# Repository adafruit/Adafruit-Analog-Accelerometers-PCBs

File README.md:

# PCBs for the Adafruit Analog Accelerometers - ADXL335, ADXL377 and ADXL326

<a href="http://www.adafruit.com/products/163"><br/>Click here to purchase one from the Adafruit shop</a>

* [ADXL335 - 5V ready triple-axis accelerometer (+-3g analog out)](https://www.adafruit.com/products/163)
* [ADXL326 - 5V ready triple-axis accelerometer (+-16g analog out)](https://www.adafruit.com/product/1018)
* [ADXL377 - High-G Triple-Axis Accelerometer (+-200g Analog Out)](https://www.adafruit.com/product/1413)

We've updated our favorite triple-axis accelerometer to now have an on-board 3.3V regulator - making it a perfect choice for interfacing with a 5V microcontroller such as the Arduino. This breakout comes with 3 analog outputs for X, Y and Z axis measurements on a 0.75"x0.75" breakout board. The ADXL335 is the latest and greatest from Analog Devices, known for their exceptional quality MEMS devices. The VCC takes up to 5V in and regulates it to 3.3V with an output pin. The analog outputs are ratiometric: that means that 0g measurement output is always at half of the 3.3V output (1.65V), -3g is at 0v and 3g is at 3.3V with full scaling in between.

Fully assembled and tested. Comes with 8 pin 0.1" standard header in case you want to use it with a breadboard or perfboard. Two 2mm (0.08") mounting holes for easy attachment.

The XYZ filter capacitors are 0.1uF for a 50 Hz bandwidth

## License

Adafruit invests time and resources providing this open source design, 
please support Adafruit and open-source hardware by purchasing 
products from Adafruit!

Designed by Adafruit Industries.  
Creative Commons Attribution, Share-Alike license, check license.txt for more information
All text above must be included in any redistribution

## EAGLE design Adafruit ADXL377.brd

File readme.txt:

These are the PCBs for the Adafruit Analog Accelerometers - ADXL335, ADXL377 and ADXL326
Format is EagleCAD schematic and board layout

For more details, check out the product page at

-----> https://www.adafruit.com/products/163
-----> https://www.adafruit.com/products/1018
-----> https://www.adafruit.com/products/1413

Adafruit invests time and resources providing this open source design, 
please support Adafruit and open-source hardware by purchasing 
products from Adafruit!

Designed by Adafruit Industries.  
Creative Commons Attribution, Share-Alike license, check license.txt for more information
All text above must be included in any redistribution

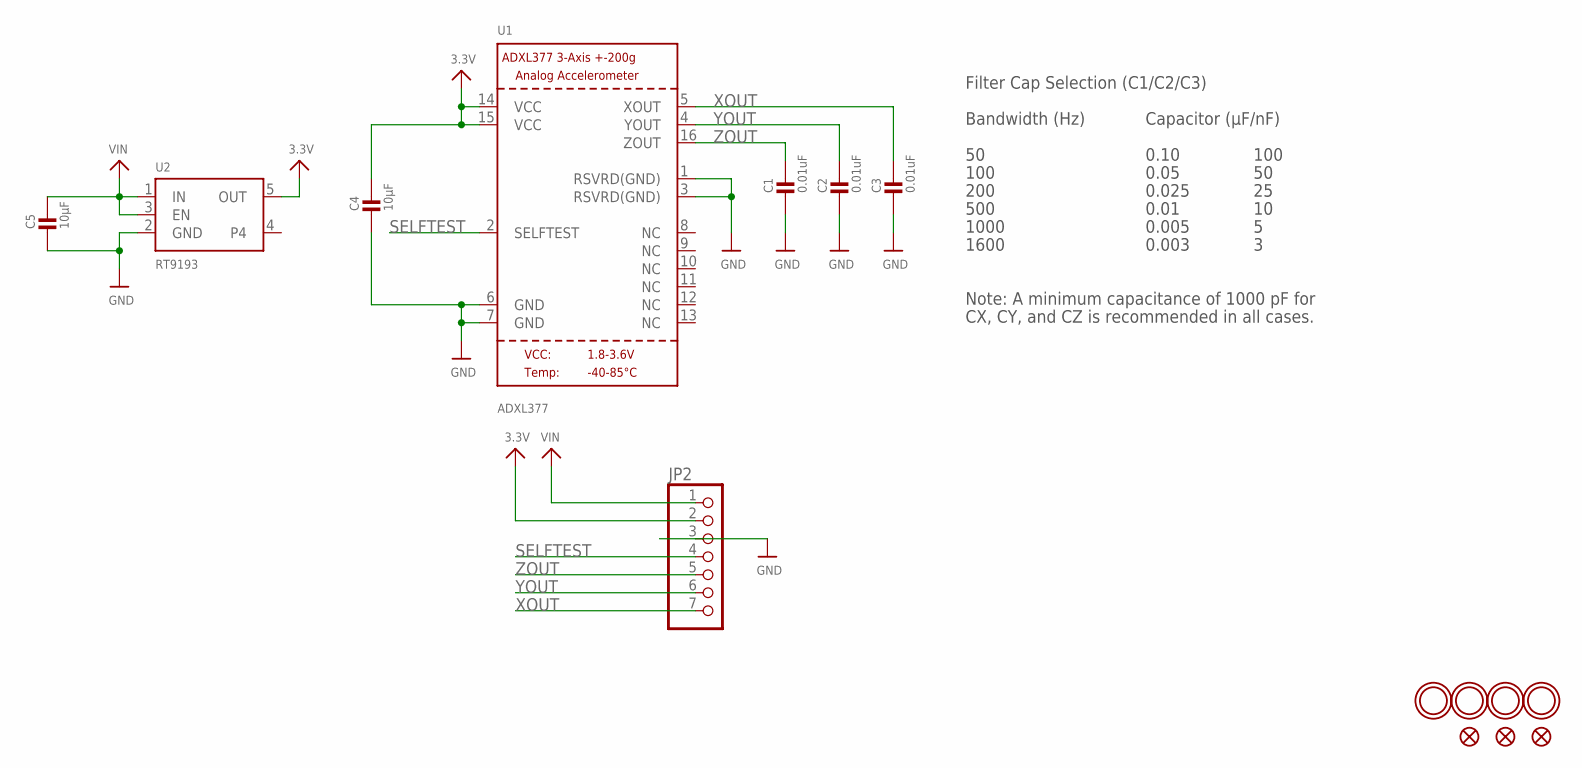
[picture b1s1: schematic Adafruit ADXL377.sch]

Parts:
C1, C2, C3: 0.01uF; _0805
C4, C5: 10µF; _0805
FID1, FID2, FID3: FIDUCIAL""; FIDUCIAL_1MM
JP2: HEADER-1X770MIL; 1X07_ROUND_70
U1: ADXL377; LFCSP16_LQ
U2: RT9193; SOT23-5
U$2, U$3, U$17, U$18: MOUNTINGHOLE2.5; MOUNTINGHOLE_2.5_PLATED

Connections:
3.3V: C4.1, JP2.2, U1.14 (VCC), U1.15 (VCC), U2.5 (OUT)
GND: C1.2, C2.2, C3.2, C4.2, C5.2, JP2.3, U1.1 (RSVRD(GND)), U1.3 (RSVRD(GND)), U1.6 (GND), U1.7 (GND), U2.2 (GND)
SELFTEST: JP2.4, U1.2 (SELFTEST)
VIN: C5.1, JP2.1, U2.1 (IN), U2.3 (EN)
XOUT: C3.1, JP2.7, U1.5 (XOUT)
YOUT: C2.1, JP2.6, U1.4 (YOUT)
ZOUT: C1.1, JP2.5, U1.16 (ZOUT)

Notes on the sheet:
Filter Cap Selection (C1/C2/C3)
Bandwidth (Hz)
Capacitor (µF/nF)
100
200
500
1000
1600
0.10
0.05
0.025
0.01
0.005
0.003
Note: A minimum capacitance of 1000 pF for
CX, CY, and CZ is recommended in all cases.

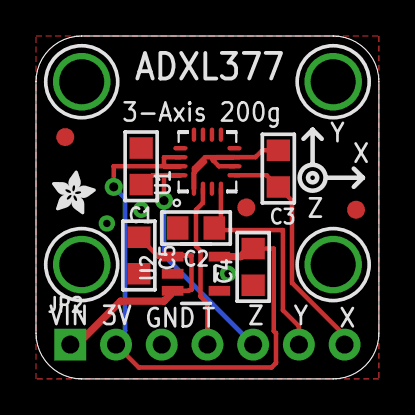
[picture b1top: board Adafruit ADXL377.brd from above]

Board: 2 copper layers, 19.0 x 19.1 mm, 17 parts (1 on the bottom side), 7 nets.

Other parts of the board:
U$16, U$19: ADAFRUIT_2.5MM

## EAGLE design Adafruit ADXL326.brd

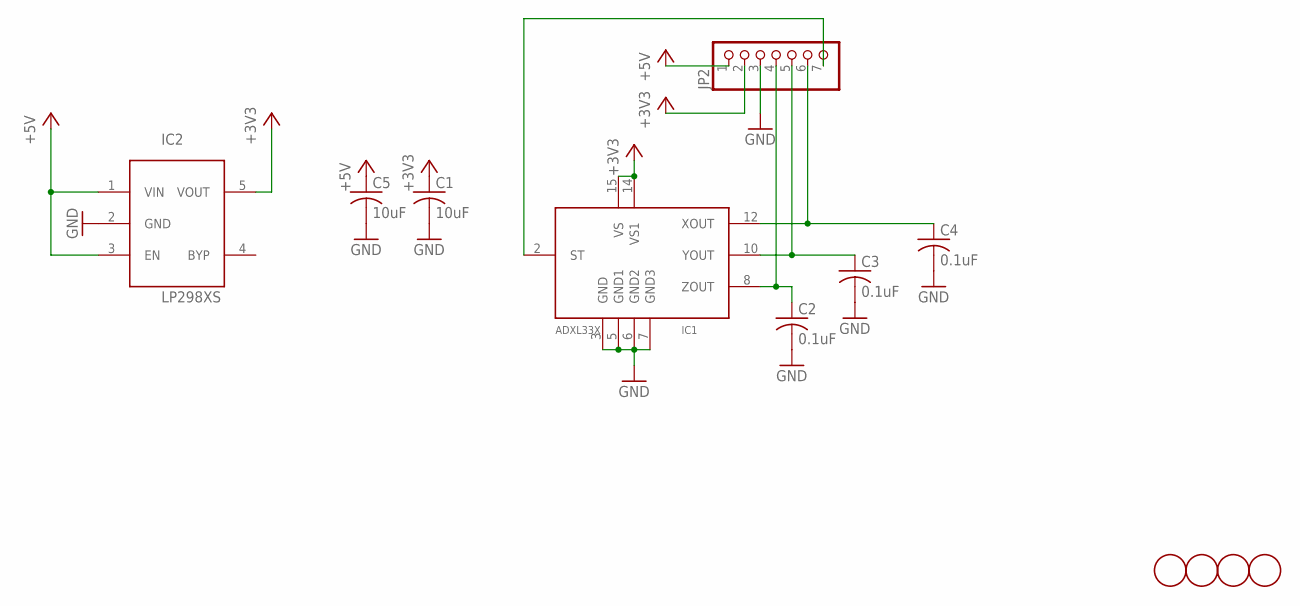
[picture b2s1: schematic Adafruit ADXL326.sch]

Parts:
C1, C5: 10uF; C0805K
C2, C3, C4: 0.1uF; C0805K
IC1: ADXL33X; 16LCSP
IC2: LP298XS; SOT23-5L
JP2: HEADER-1X7THICKER; 1X07_ROUND_76
U$1, U$2: FIDUCIAL; FIDUCIAL_1MM
U$5, U$8: MOUNTINGHOLE2.0; MOUNTINGHOLE_2.0_PLATED

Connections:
+3V3: C1.1, IC1.14 (VS1), IC1.15 (VS), IC2.5 (VOUT), JP2.2
+5V: C5.1, IC2.1 (VIN), IC2.3 (EN), JP2.1
GND: C1.2, C2.2, C3.2, C4.2, C5.2, IC1.3 (GND), IC1.5 (GND1), IC1.6 (GND2), IC1.7 (GND3), IC2.2 (GND), JP2.3
ST: IC1.2 (ST), JP2.7
XOUT: C4.1, IC1.12 (XOUT), JP2.6
YOUT: C3.1, IC1.10 (YOUT), JP2.5
ZOUT: C2.1, IC1.8 (ZOUT), JP2.4

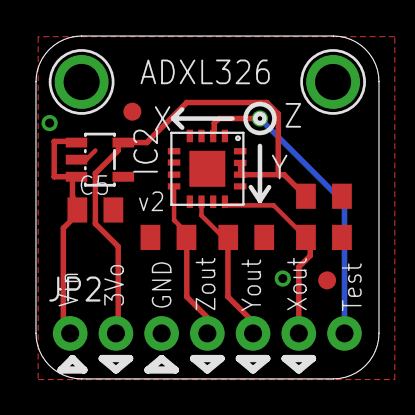
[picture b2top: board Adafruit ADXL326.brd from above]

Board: 2 copper layers, 19.1 x 19.1 mm, 13 parts (1 on the bottom side), 7 nets.

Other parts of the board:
U$4: ADAFRUIT_2.5MM

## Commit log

2012-11-05 Eagle Cad for ADXL326 and ADXL335
2012-11-05 read me!
2013-10-04 added adxl377
2013-10-04 read
2019-05-16 readme + image + license

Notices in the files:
parts and their libraries:
microbuilder: This work is placed in the public domain, and may be freely used for commercial and non-commercial work with the following conditions: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
